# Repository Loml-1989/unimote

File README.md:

# Universal Bluetooth IR Remote
A compact universal infrared (IR) remote control powered by an ESP32 C3. It connects to your mobile phone via Bluetooth, allowing you to capture IR codes and blast them from your phone.
## Features
- **Wireless Bluetooth Connectivity:** Connects with phone to control.
- **IR Capturing & Emitting:** TSOP38238 receiver to capture signals and an IR LED blasts packages.
- **Rechargeable & Portable:** Powered by a 3.7V LiPo battery.
- **Custom PCB Design:** Built around the smol Seeed Studio XIAO ESP32-C3.
## Hardware Specs
- **Microcontroller:** Seeed Studio XIAO ESP32 C3 (SMD)
- **IR Receiver:** TSOP38238
- **IR Transmitter:** 940nm IR LED driven by a BC547 NPN Transistor
- **Power:** 3.7V LiPo Battery
## Firmware Setup
The firmware is vibe coded and untested because I didn't make the device yet.
### Library Required
**IRremote** by shirriff

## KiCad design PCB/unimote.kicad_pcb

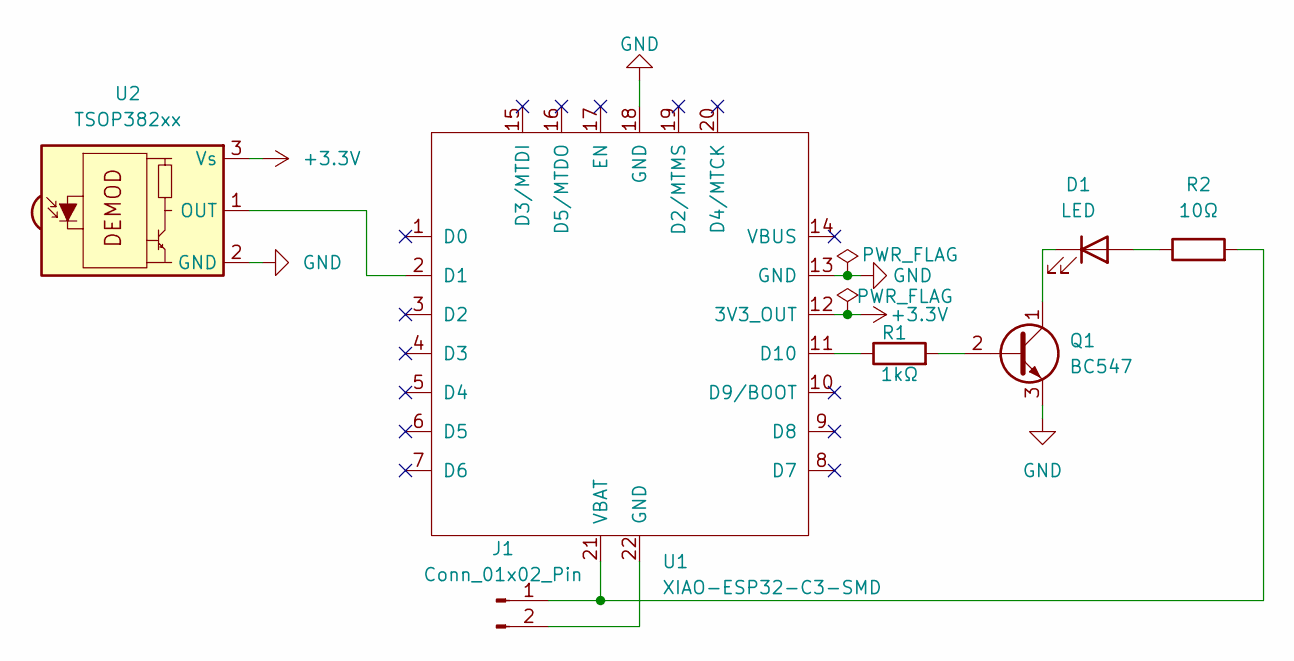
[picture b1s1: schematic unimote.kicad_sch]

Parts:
D1: LED; LED_D5.0mm
J1: Conn_01x02_Pin; JST_PH_B2B-PH-K_1x02_P2.00mm_Vertical
Q1: BC547; TO-92_Inline
R1: 1kΩ; R_0805_2012Metric_Pad1.20x1.40mm_HandSolder
R2: 10Ω; R_0805_2012Metric_Pad1.20x1.40mm_HandSolder
U1: XIAO-ESP32-C3-SMD
U2: TSOP382xx; Vishay_MINICAST-3Pin

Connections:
+3.3V: U1.12 (3V3_OUT), U2.3 (Vs)
GND: Q1.3 (E), U1.13 (GND), U1.18 (GND), U2.2 (GND)
unnamed: D1.2 (A), R2.1
unnamed: D1.1 (K), Q1.1 (C)
unnamed: J1.1, R2.2, U1.21 (VBAT)
unnamed: J1.2, U1.22 (GND)
unnamed: Q1.2 (B), R1.2
unnamed: U1.2 (D1), U2.1 (OUT)
unnamed: R1.1, U1.11 (D10)

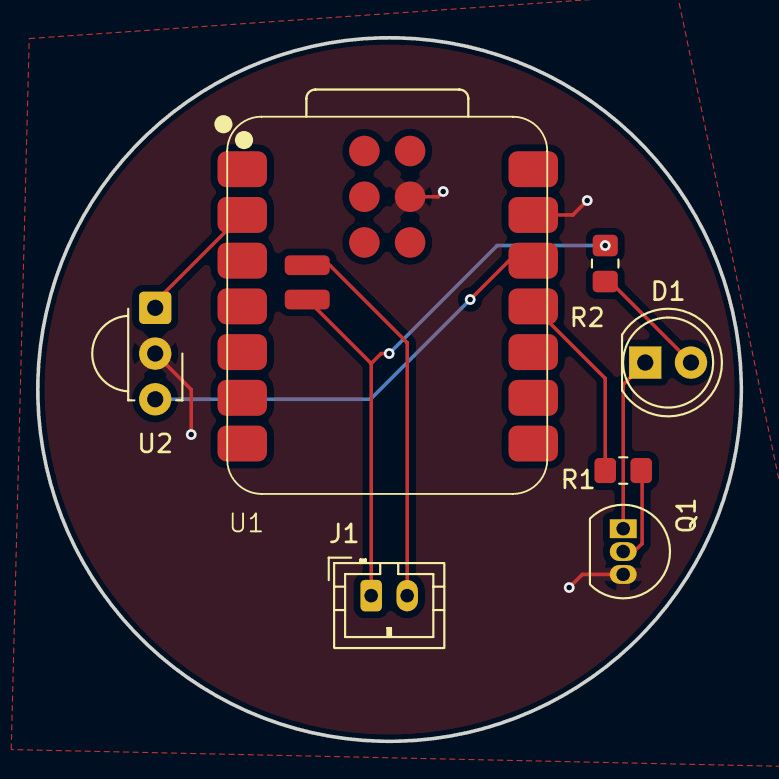
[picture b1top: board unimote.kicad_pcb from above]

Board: 2 copper layers, 39.1 x 39.1 mm, 7 parts (0 on the bottom side), 9 nets.
